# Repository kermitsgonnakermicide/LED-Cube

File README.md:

# LED-Cube
**it is led. it is cube. it is soup**

assembly guide </br>
- print and assemble TWO of these boards(you dont need the MCU on the second board but id want to get rid of it so ehh)
- get your lipo battery and mini step down converter
- solder all the headers together(of all 6 panels) and connect the microcontroller box(on the inside)

> bibi netanyahu

> schematic

> 3d

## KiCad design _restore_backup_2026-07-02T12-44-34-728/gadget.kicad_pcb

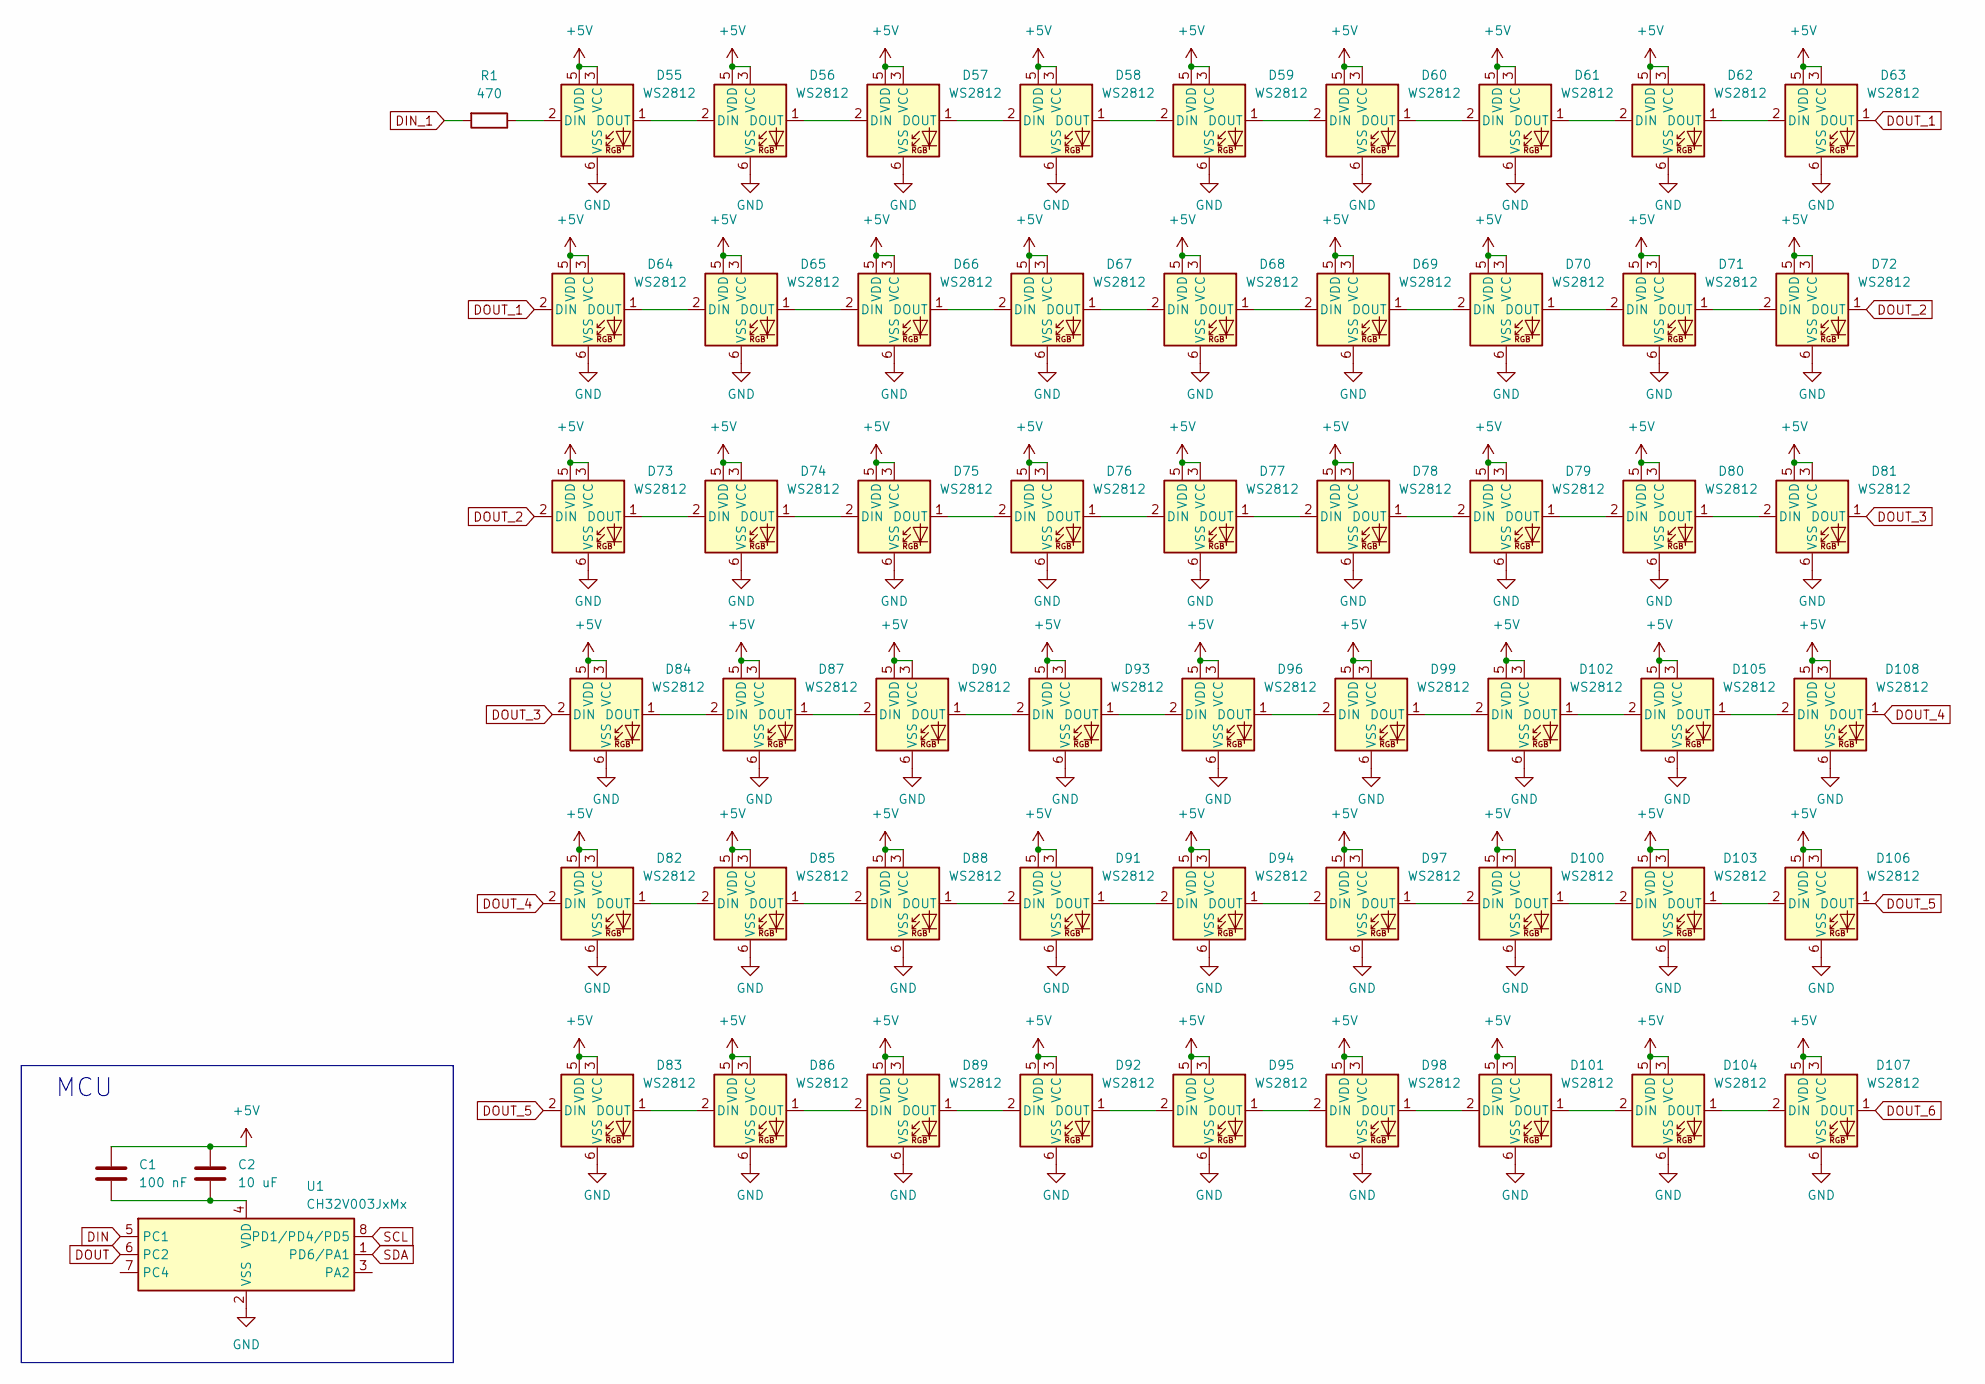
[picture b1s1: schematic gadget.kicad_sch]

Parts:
C1: 100 nF; C_0805_2012Metric_Pad1.18x1.45mm_HandSolder
C2: 10 uF; C_0805_2012Metric_Pad1.18x1.45mm_HandSolder
D55, D56, D57, D58, D59, D60, D61, D62, D63, D64, D65, D66, D67, D68, D69, D70, D71, D72, D73, D74, D75, D76, D77, D78, D79, D80, D81, D82, D83, D84, D85, D86, D87, D88, D89, D90, D91, D92, D93, D94, D95, D96, D97, D98, D99, D100, D101, D102, D103, D104, D105, D106, D107, D108: WS2812; LED_WS2812_PLCC6_5.0x5.0mm_P1.6mm
R1: 470; R_0805_2012Metric_Pad1.20x1.40mm_HandSolder
U1: CH32V003JxMx; JEITA_SOIC-8_3.9x4.9mm_P1.27mm

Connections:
+5V: C1.2, C2.2, D55.3 (VCC), D55.5 (VDD), D56.3 (VCC), D56.5 (VDD), D57.3 (VCC), D57.5 (VDD), D58.3 (VCC), D58.5 (VDD), D59.3 (VCC), D59.5 (VDD), D60.3 (VCC), D60.5 (VDD), D61.3 (VCC), D61.5 (VDD), D62.3 (VCC), D62.5 (VDD), D63.3 (VCC), D63.5 (VDD), D64.3 (VCC), D64.5 (VDD), D65.3 (VCC), D65.5 (VDD), D66.3 (VCC), D66.5 (VDD), D67.3 (VCC), D67.5 (VDD), D68.3 (VCC), D68.5 (VDD), D69.3 (VCC), D69.5 (VDD), D70.3 (VCC), D70.5 (VDD), D71.3 (VCC), D71.5 (VDD), D72.3 (VCC), D72.5 (VDD), D73.3 (VCC), D73.5 (VDD), D74.3 (VCC), D74.5 (VDD), D75.3 (VCC), D75.5 (VDD), D76.3 (VCC), D76.5 (VDD), D77.3 (VCC), D77.5 (VDD), D78.3 (VCC), D78.5 (VDD), D79.3 (VCC), D79.5 (VDD), D80.3 (VCC), D80.5 (VDD), D81.3 (VCC), D81.5 (VDD), D82.3 (VCC), D82.5 (VDD), D83.3 (VCC), D83.5 (VDD), D84.3 (VCC), D84.5 (VDD), D85.3 (VCC), D85.5 (VDD), D86.3 (VCC), D86.5 (VDD), D87.3 (VCC), D87.5 (VDD), D88.3 (VCC), D88.5 (VDD), D89.3 (VCC), D89.5 (VDD), D90.3 (VCC), D90.5 (VDD), D91.3 (VCC), D91.5 (VDD), D92.3 (VCC), D92.5 (VDD), D93.3 (VCC), D93.5 (VDD), D94.3 (VCC), D94.5 (VDD), D95.3 (VCC), D95.5 (VDD), D96.3 (VCC), D96.5 (VDD), D97.3 (VCC), D97.5 (VDD), D98.3 (VCC), D98.5 (VDD), D99.3 (VCC), D99.5 (VDD), D100.3 (VCC), D100.5 (VDD), D101.3 (VCC), D101.5 (VDD), D102.3 (VCC), D102.5 (VDD), D103.3 (VCC), D103.5 (VDD), D104.3 (VCC), D104.5 (VDD), D105.3 (VCC), D105.5 (VDD), D106.3 (VCC), D106.5 (VDD), D107.3 (VCC), D107.5 (VDD), D108.3 (VCC), D108.5 (VDD)
DIN: U1.5 (PC1)
DIN_1: R1.2
DOUT: U1.6 (PC2)
DOUT_1: D63.1 (DOUT), D64.2 (DIN)
DOUT_2: D72.1 (DOUT), D73.2 (DIN)
DOUT_3: D81.1 (DOUT), D84.2 (DIN)
DOUT_4: D82.2 (DIN), D108.1 (DOUT)
DOUT_5: D83.2 (DIN), D106.1 (DOUT)
DOUT_6: D107.1 (DOUT)
GND: D55.6 (VSS), D56.6 (VSS), D57.6 (VSS), D58.6 (VSS), D59.6 (VSS), D60.6 (VSS), D61.6 (VSS), D62.6 (VSS), D63.6 (VSS), D64.6 (VSS), D65.6 (VSS), D66.6 (VSS), D67.6 (VSS), D68.6 (VSS), D69.6 (VSS), D70.6 (VSS), D71.6 (VSS), D72.6 (VSS), D73.6 (VSS), D74.6 (VSS), D75.6 (VSS), D76.6 (VSS), D77.6 (VSS), D78.6 (VSS), D79.6 (VSS), D80.6 (VSS), D81.6 (VSS), D82.6 (VSS), D83.6 (VSS), D84.6 (VSS), D85.6 (VSS), D86.6 (VSS), D87.6 (VSS), D88.6 (VSS), D89.6 (VSS), D90.6 (VSS), D91.6 (VSS), D92.6 (VSS), D93.6 (VSS), D94.6 (VSS), D95.6 (VSS), D96.6 (VSS), D97.6 (VSS), D98.6 (VSS), D99.6 (VSS), D100.6 (VSS), D101.6 (VSS), D102.6 (VSS), D103.6 (VSS), D104.6 (VSS), D105.6 (VSS), D106.6 (VSS), D107.6 (VSS), D108.6 (VSS), U1.2 (VSS)
unnamed: D55.2 (DIN), R1.1
unnamed: D55.1 (DOUT), D56.2 (DIN)
unnamed: D56.1 (DOUT), D57.2 (DIN)
unnamed: D57.1 (DOUT), D58.2 (DIN)
unnamed: D58.1 (DOUT), D59.2 (DIN)
unnamed: D59.1 (DOUT), D60.2 (DIN)
unnamed: D60.1 (DOUT), D61.2 (DIN)
unnamed: D61.1 (DOUT), D62.2 (DIN)
unnamed: D62.1 (DOUT), D63.2 (DIN)
unnamed: D64.1 (DOUT), D65.2 (DIN)
unnamed: D65.1 (DOUT), D66.2 (DIN)
unnamed: D66.1 (DOUT), D67.2 (DIN)
unnamed: D67.1 (DOUT), D68.2 (DIN)
unnamed: D68.1 (DOUT), D69.2 (DIN)
unnamed: D69.1 (DOUT), D70.2 (DIN)
unnamed: D70.1 (DOUT), D71.2 (DIN)
unnamed: D71.1 (DOUT), D72.2 (DIN)
unnamed: D73.1 (DOUT), D74.2 (DIN)
unnamed: D74.1 (DOUT), D75.2 (DIN)
unnamed: D75.1 (DOUT), D76.2 (DIN)
unnamed: D76.1 (DOUT), D77.2 (DIN)
unnamed: D77.1 (DOUT), D78.2 (DIN)
unnamed: D78.1 (DOUT), D79.2 (DIN)
unnamed: D79.1 (DOUT), D80.2 (DIN)
unnamed: D80.1 (DOUT), D81.2 (DIN)
unnamed: D82.1 (DOUT), D85.2 (DIN)
unnamed: D83.1 (DOUT), D86.2 (DIN)
unnamed: D84.1 (DOUT), D87.2 (DIN)
unnamed: D85.1 (DOUT), D88.2 (DIN)
unnamed: D86.1 (DOUT), D89.2 (DIN)
unnamed: D87.1 (DOUT), D90.2 (DIN)
unnamed: D88.1 (DOUT), D91.2 (DIN)
unnamed: D89.1 (DOUT), D92.2 (DIN)
unnamed: D90.1 (DOUT), D93.2 (DIN)
unnamed: D91.1 (DOUT), D94.2 (DIN)
unnamed: D92.1 (DOUT), D95.2 (DIN)
unnamed: D93.1 (DOUT), D96.2 (DIN)
unnamed: D94.1 (DOUT), D97.2 (DIN)
unnamed: D95.1 (DOUT), D98.2 (DIN)
unnamed: D96.1 (DOUT), D99.2 (DIN)
unnamed: D97.1 (DOUT), D100.2 (DIN)
unnamed: D100.1 (DOUT), D103.2 (DIN)
unnamed: D98.1 (DOUT), D101.2 (DIN)
unnamed: D101.1 (DOUT), D104.2 (DIN)
unnamed: D99.1 (DOUT), D102.2 (DIN)
unnamed: D102.1 (DOUT), D105.2 (DIN)
unnamed: D103.1 (DOUT), D106.2 (DIN)
unnamed: D104.1 (DOUT), D107.2 (DIN)
unnamed: D105.1 (DOUT), D108.2 (DIN)
unnamed: C1.1, C2.1, U1.4 (VDD)
SCL: U1.8 (PD1/PD4/PD5)
SDA: U1.1 (PD6/PA1)

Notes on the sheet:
MCU

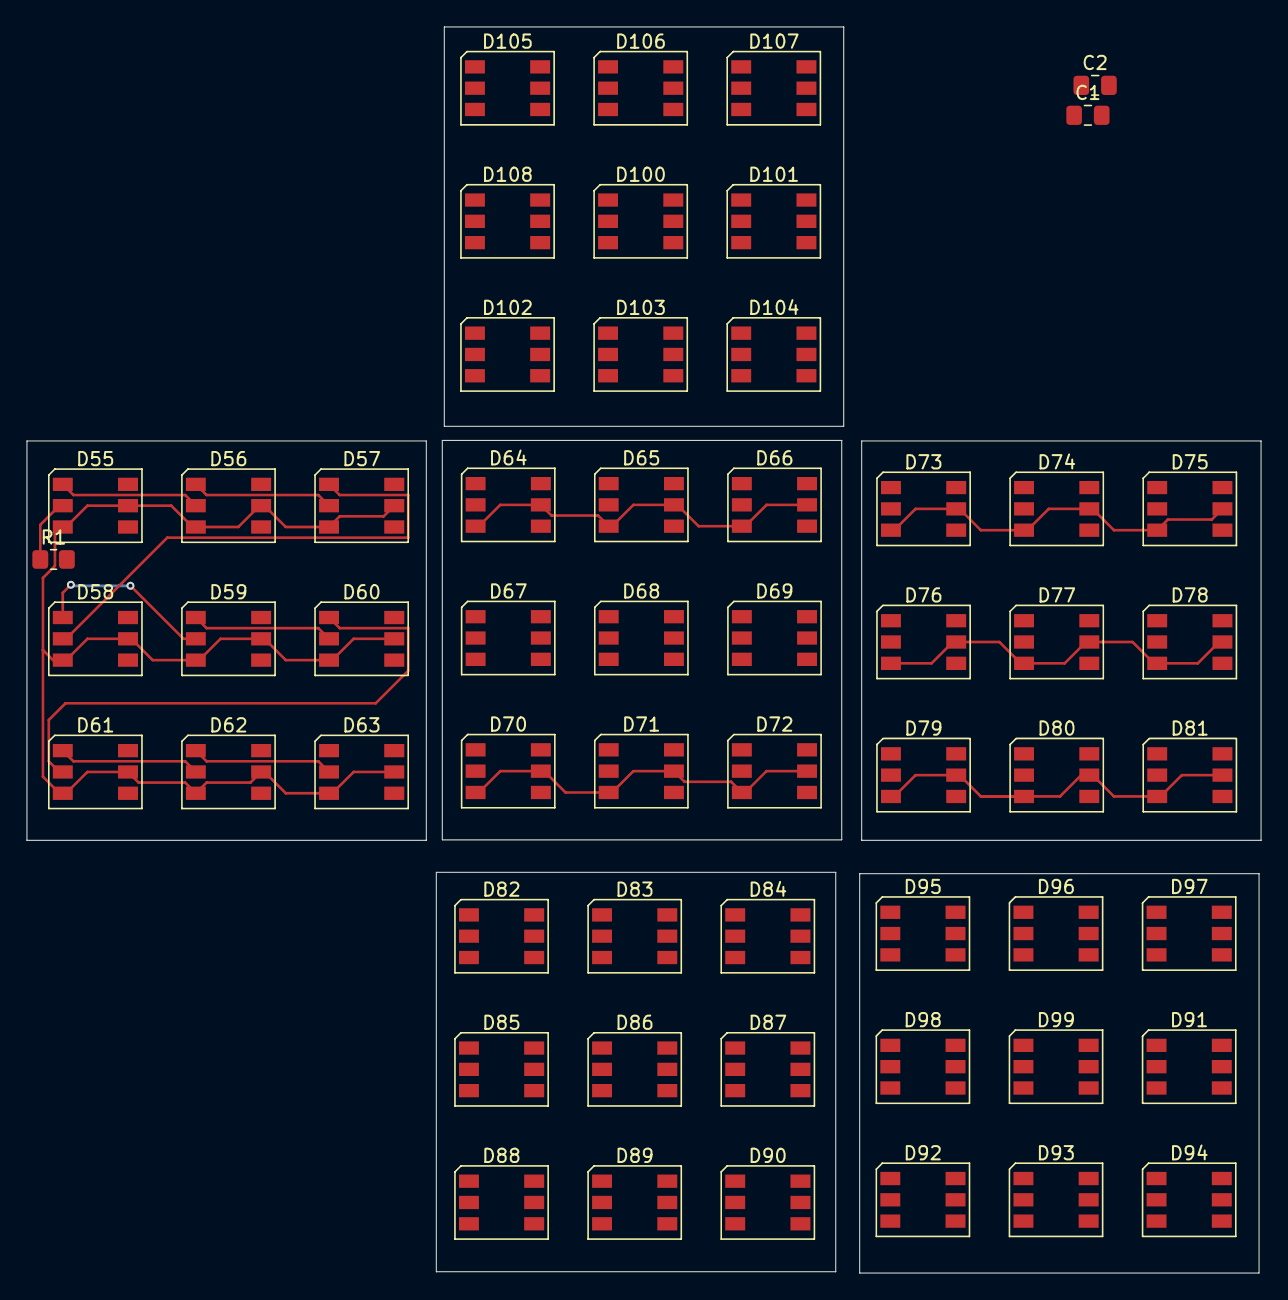
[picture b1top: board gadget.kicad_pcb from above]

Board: 2 copper layers, 92.7 x 93.6 mm, 58 parts (1 on the bottom side), 57 nets.
